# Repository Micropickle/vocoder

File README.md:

# THE VOCODER

a voice amplifier for use with encumbersome masks such as gas masks

## breif description
the vocoder is a device that allows you to alter your voice to your specifications and allows you to amplify it through speakers and bone transducer speakers and is especially useful in situations where wearing a mask can muffle your voice.

## inspiration
the project was first inspired by a fictonal story/world called degenesis where people called chroniclers disguised their voices using vocoders, long tubes went down their throats to gather their voice and was fed into the 'vocoder' which then was distorted and was amplifiable. along with that i own masks and gasmasks that make it hard to communicate with others so the device is meant to gather your voice via a mic or throat mic and output it via speakers or bone transducer speakers placed on the mask itself which is very useful for hobbies such as airsofting or cosplaying. the device also has professional use cases such as when having to wear heavy clothing and gasmasks such as PPE, this device will make you clearly audible to others when working

## gallery

CAD designs
`photos/CAD designs/KiCad`

initial prototype photos
`photos/prototype version`

## how to use
1. plug in mic of your choice (the standard is the audio jack port found in phones, but the board can be modified for different ports) and wire in an external speaker that meets the specifications of the amplifier chip
2. compile the project on Platformio and flash to the board (this is necessary as in the future i will implement configurations for BLE and initial settings for audio modification such as amplification, distortion, pitch changing, etc.)
3. wire in audio output of your choosing

## bill of materials

`hardware/production/bom.csv`

## initial prototype
it started off as a proof of concept through a prototype board using a simple XIAO esp32 c3 to test the idea and the limitations, this taught me alot digital audio, sound systems and BLE as all three are very necessary for this project

the issue was everything was powered by the 3v3 pin on the esp, i had to rely on an external amplifier (and external power supply) to make it work, furthermore the esp's clock speed was too slow and brought about glitches in the audio output. 

## description
the circuit board went through many design stages primarily due to three things, errors, expense and having to include extra components to make the circuit work properly.

the main parts of the circuit are as followed
* the esp32-s3 board was chosen for its high clockspeed, familiarity and extensive functionality, the esp32-s3 WROOM board had included wifi, bluetooth, BLE and usb pins reducing external circuits needed and opening up options in terms of customisation
* the ADAU1761 is a codec that includes a ADC, DAC and built in processor to make changes to the incoming and outcoming audio, this was chosen due to its specialty in audio processing which will reduce the processing power from the esp32 and its ease of programming due to the manufacturers having dedicated graphical software for the chip, the only problem is custom drivers need to be written for the esp32 to upload the code for the ADAU1761
* the MAX98357A was chosen due to its bilt in i2s interfacw which is compatable with the esp32 and the adau1761 as both can be interfaced with the i2s bus, an amplifier was included so that the audio output can be directed to a speaker or bone transucer without an external amplifier or power supply

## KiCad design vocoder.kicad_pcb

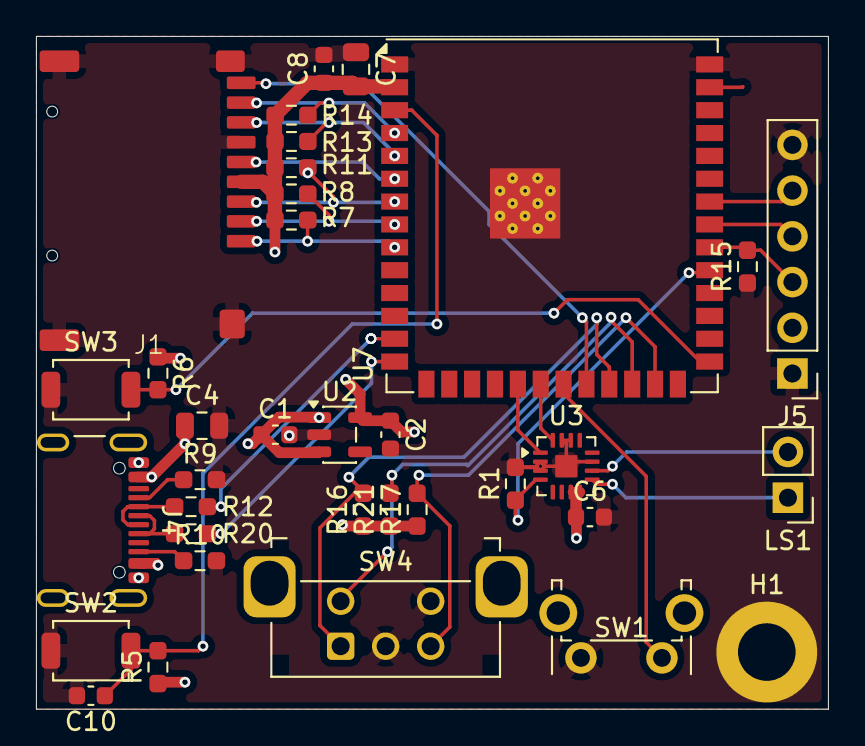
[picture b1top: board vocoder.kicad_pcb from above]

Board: 4 copper layers, 44.0 x 37.4 mm, 35 parts (0 on the bottom side), 30 nets.

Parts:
C1, C2, C6, C8: 1u; C_0603_1608Metric
C4, C7: 10u; C_0805_2012Metric
C10: 0.1u; C_0603_1608Metric
H1: MountingHole_Pad; MountingHole_3.2mm_M3_DIN965_Pad
J1: Micro_SD_Card_Det1; Untitled
J4: USB_C_Receptacle_USB2.0_16P; USB_C_Receptacle_GCT_USB4105-xx-A_16P_TopMnt_Horizontal
J5: Conn_02x03_Top_Bottom; PinHeader_1x06_P2.54mm_Vertical
LS1: Speaker; PinHeader_1x02_P2.54mm_Vertical
R1, R5, R6, R7, R8, R11, R13, R14, R16, R17, R21: 10k; R_0603_1608Metric_Pad0.98x0.95mm_HandSolder
R9, R10: 5.1k; R_0603_1608Metric_Pad0.98x0.95mm_HandSolder
R12, R20: 27; R_0603_1608Metric_Pad0.98x0.95mm_HandSolder
R15: 100k; R_0603_1608Metric_Pad0.98x0.95mm_HandSolder
SW1: SW_Push; SW_Tactile_SPST_Angled_PTS645Vx58-2LFS
SW2, SW3: SW_Push; SW_SPST_TS-1088-xR020
SW4: RotaryEncoder_Switch; RotaryEncoder_Bourns_Horizontal_PEC12R-2x17F-Sxxxx
U2: AP2112K-3.3; SOT-23-5
U3: MAX98357A; TQFN-16-1EP_3x3mm_P0.5mm_EP1.23x1.23mm
U7: ESP32-S3-WROOM-1; ESP32-S3-WROOM-1U

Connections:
3V3: C2.1, C7.2, C8.1, J1.4 (VDD), J5.2, R5.1, R6.1, R7.1, R8.1, R11.1, R13.1, R14.1, R16.1, R17.1, R21.1, U2.5 (VOUT), U7.2 (3V3)
AMP_SWITCH: R1.1, U3.4 (~SD_MODE), U7.31 (IO38)
BOOT: R6.2, SW3.2, U7.27 (IO0)
BUTTON_READ: SW1.1, U7.21 (IO13)
CLK: J1.5 (CLK), U7.6 (IO6)
CMD: J1.3 (CMD), R11.2, U7.7 (IO7)
D0: J1.7 (DAT0), R13.2, U7.5 (IO5)
D1: J1.8 (DAT1), R14.2, U7.4 (IO4)
D2: J1.1 (DAT2), R7.2, U7.9 (IO16)
D3: J1.2 (DAT3/CD), R8.2, U7.8 (IO15)
DET: J1.9 (DET), U7.22 (IO14)
EN: C10.1, R5.2, SW2.2, U7.3 (EN)
ENC_LEFT: R16.2, SW4.A, U7.23 (IO21)
ENC_PUSH: R21.2, SW4.S1, U7.24 (IO47)
ENC_RIGHT: R17.2, SW4.B, U7.25 (IO48)
GND: C1.2, C2.2, C4.2, C6.2, C7.1, C8.2, C10.2, H1.1 (1_1), J1.6 (VSS), J1.SH (SHIELD), J4.A1 (GND), J4.A12 (GND), J4.B1 (GND), J4.B12 (GND), J5.1, J5.6, R1.2, R9.2, R10.2, R15.1, SW1.2, SW2.1, SW3.1, SW4.C, SW4.S2, U2.2 (GND), U3.2 (GAIN_SLOT), U3.3 (GND), U3.11 (GND), U3.14 (LRCLK), U3.15 (GND), U3.17 (PAD), U7.1 (GND), U7.40 (GND), U7.41 (GND)
I2S_BCLK_MIC: J5.4, U7.33 (IO40)
I2S_BCLK_SPEAKER: U3.16 (BCLK), U7.20 (IO12)
I2S_DATA_IN: J5.3, R15.2, U7.32 (IO39)
I2S_DATA_OUT: U3.1 (DIN), U7.19 (IO11)
I2S_WS: J5.5, U7.34 (IO41)
unnamed: J4.A5 (CC1), R9.1
unnamed: J4.B5 (CC2), R10.1
unnamed: J4.A6 (D+), J4.B6 (D+), R20.1
unnamed: J4.A7 (D-), J4.B7 (D-), R12.1
unnamed: LS1.2, U3.10 (OUTN)
unnamed: LS1.1, U3.9 (OUTP)
USB+: R20.2, U7.14 (USB_D+)
USB-: R12.2, U7.13 (USB_D-)
USB_5V: C1.1, C4.1, C6.1, J4.A4 (VBUS), J4.A9 (VBUS), J4.B4 (VBUS), J4.B9 (VBUS), U2.1 (VIN), U2.3 (EN), U3.7 (VDD), U3.8 (VDD)

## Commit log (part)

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2026-01-22 mistake
2026-01-22 hardware complete
2026-01-22 oops
2026-01-23 photos
2026-01-23 readme file
2026-01-27 Revise README with project details and BOM
    Updated README.md to include additional information about the vocoder project, including a general buying section for common components and a more detailed bill of materials.
2026-01-27 changed sizes to JLCPCB acceptable sizes
2026-01-30 changed firware, improved audio
2026-02-12 fixed component placement
2026-02-12 placed bom file in root diretory
2026-02-13 fixed grounding pad not attatched to ground plane
2026-02-13 commited with open files by accident
2026-03-05 complete redesign of board and circuit, smaller and more powerful
2026-03-05 fixed minor error
2026-03-05 added screenshots of the new design
2026-03-05 Revise README with updated project details
    Updated the README to reflect new images and descriptions.
2026-03-05 bom file didnt feel like updating
2026-03-06 trying to fix bom
2026-03-09 fixing production files
2026-03-09 changed buttons to smaller SMT ones
2026-03-09 added BOM
2026-04-20 added debug led's
2026-04-20 file cleanup
2026-06-26 working circuit without amplifier
